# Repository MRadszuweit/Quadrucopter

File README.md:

# Quadrucopter

This repository contains two directories: one with C-code communication of the computer 
with an xbee module via an emulated com port by a FT232 connected to the usb port. 
The other directory contains AVR-C code running on the quadrucopters hardware (ATMEGA64 and ATMEGA8) 
and Eagle files for the electronic layout of different components.

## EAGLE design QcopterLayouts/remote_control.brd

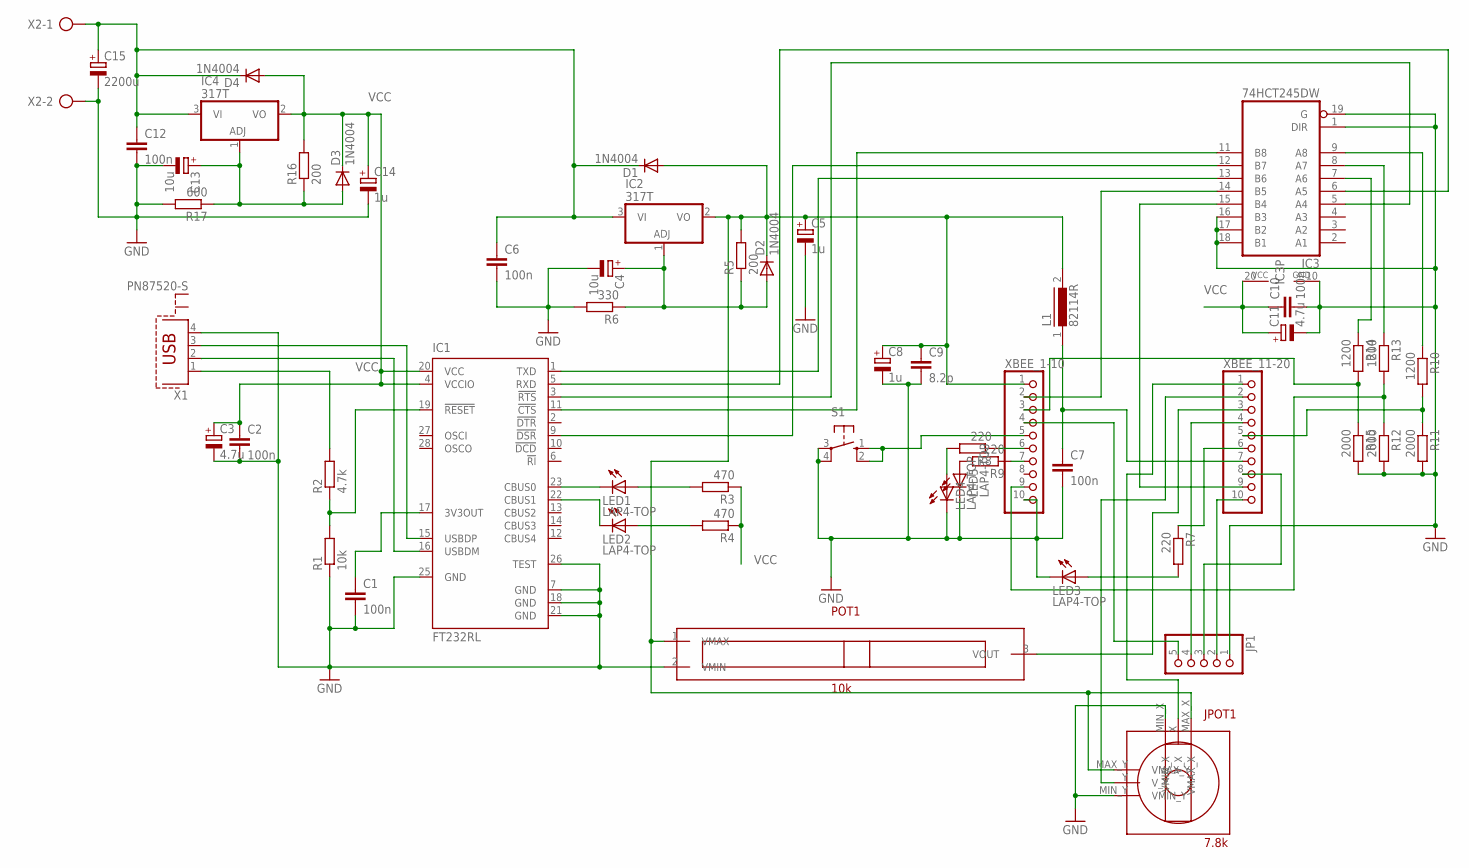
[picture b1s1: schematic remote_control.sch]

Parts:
C1, C6, C7, C12: 100n; C025-030X050
C2, C10: 100n; C0805K
C3, C11: 4.7u; 153CLV-0605
C4, C13: 10u; E5-8,5
C5, C8, C14: 1u; E5-8,5
C9: 8.2p; C025-030X050
C15: 2200u; EB20D
D1, D2, D3, D4: 1N4004; DO41-10
IC1: FT232RL; SSOP28
IC2, IC4: 317T; TO220H
IC3: 74HCT245DW; SO20W
JP1: PINHD-1X5; 1X05
JPOT1: 7.8k; DIL
L1: 82114R
LED1, LED2, LED3, LED4, LED5: LAP4-TOP; P47F-TOP
POT1: 10k; DIL
R1: 10k; 0207/10
R2: 4.7k; 0207/10
R3, R4: 470; 0207/10
R5, R16: 200; 0411/15
R6: 330; 0411/15
R7, R8, R9: 220; 0207/10
R10, R13, R14: 1200; 0207/10
R11, R12, R15: 2000; 0207/10
R17: 600; 0411/15
S1: 40-XX; B3F-40XX
X1: PN87520-S
X2: AK300/2
XBEE_1-10, XBEE_11-20: PINHD-1X10M; 1X10M

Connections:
GND: C1.2, C2.2, C3.-, C4.-, C5.-, C6.2, C7.2, C8.-, C9.2, C10.2, C11.-, C12.2, C13.-, C14.-, C15.-, IC1.7 (GND), IC1.18 (GND), IC1.21 (GND), IC1.25 (GND), IC1.26 (TEST), IC3.1 (DIR), IC3.10 (GND), IC3.16 (B3), IC3.17 (B2), IC3.18 (B1), IC3.19 (G), JP1.1, JPOT1.MIN_X (VMIN_X), JPOT1.MIN_Y (VMIN_Y), LED3.C, LED4.C, LED5.C, POT1.2 (VMIN), R1.1, R6.2, R11.2, R12.2, R15.2, R17.2, S1.3, S1.4 (P1), X1.4, X2.2, XBEE_1-10.10
unnamed: R2.2, X1.1
unnamed: IC1.19 (!RESET), R1.2, R2.1
unnamed: IC1.16 (USBDM), X1.2
unnamed: IC1.15 (USBDP), X1.3
unnamed: C1.1, IC1.17 (3V3OUT)
unnamed: S1.1 (S), S1.2 (S1), XBEE_1-10.5
unnamed: C4.+, D2.A, IC2.1 (ADJ), R5.1, R6.1
unnamed: LED3.A, R7.2
unnamed: IC1.23 (CBUS0), LED1.C
unnamed: IC1.22 (CBUS1), LED2.C
unnamed: LED1.A, R3.2
unnamed: LED2.A, R4.2
unnamed: R7.1, XBEE_11-20.6
unnamed: C7.1, L1.1, XBEE_11-20.7
unnamed: C5.+, C8.+, C9.1, D1.A, D2.C, IC2.2 (VO), JPOT1.MAX_X (VMAX_X), JPOT1.MAX_Y (VMAX_Y), L1.2, POT1.1 (VMAX), R5.2, XBEE_1-10.1
unnamed: R8.1, XBEE_1-10.6
unnamed: LED4.A, R8.2
unnamed: R9.1, XBEE_1-10.7
unnamed: LED5.A, R9.2
unnamed: IC3.9 (A8), R10.1
unnamed: R10.2, R11.1, XBEE_11-20.5
unnamed: R12.1, R13.2, XBEE_1-10.9
unnamed: IC1.11 (!CTS), IC3.11 (B8)
unnamed: IC3.8 (A7), R13.1
unnamed: IC1.9 (!DSR), IC3.12 (B7)
unnamed: R14.2, R15.1, XBEE_1-10.3
unnamed: IC3.7 (A6), R14.1
unnamed: JP1.2, XBEE_11-20.10
unnamed: IC1.1 (TXD), IC3.13 (B6)
unnamed: IC1.5 (RXD), IC3.6 (A5)
unnamed: IC3.14 (B5), XBEE_1-10.2
unnamed: IC1.3 (!RTS), IC3.5 (A4)
unnamed: IC3.15 (B4), XBEE_11-20.9
unnamed: JP1.3, XBEE_11-20.8
unnamed: JP1.4, XBEE_11-20.4
unnamed: JP1.5, XBEE_1-10.4
unnamed: POT1.3 (VOUT), XBEE_11-20.3
unnamed: JPOT1.X (V_X), XBEE_11-20.1
unnamed: JPOT1.Y (V_Y), XBEE_11-20.2
unnamed: C13.+, D3.A, IC4.1 (ADJ), R16.1, R17.1
V: C6.1, C12.1, C15.+, D1.C, D4.C, IC2.3 (VI), IC4.3 (VI), X2.1
VCC: C2.1, C3.+, C10.1, C11.+, C14.+, D3.C, D4.A, IC1.4 (VCCIO), IC1.20 (VCC), IC3.20 (VCC), IC4.2 (VO), R3.1, R4.1, R16.2

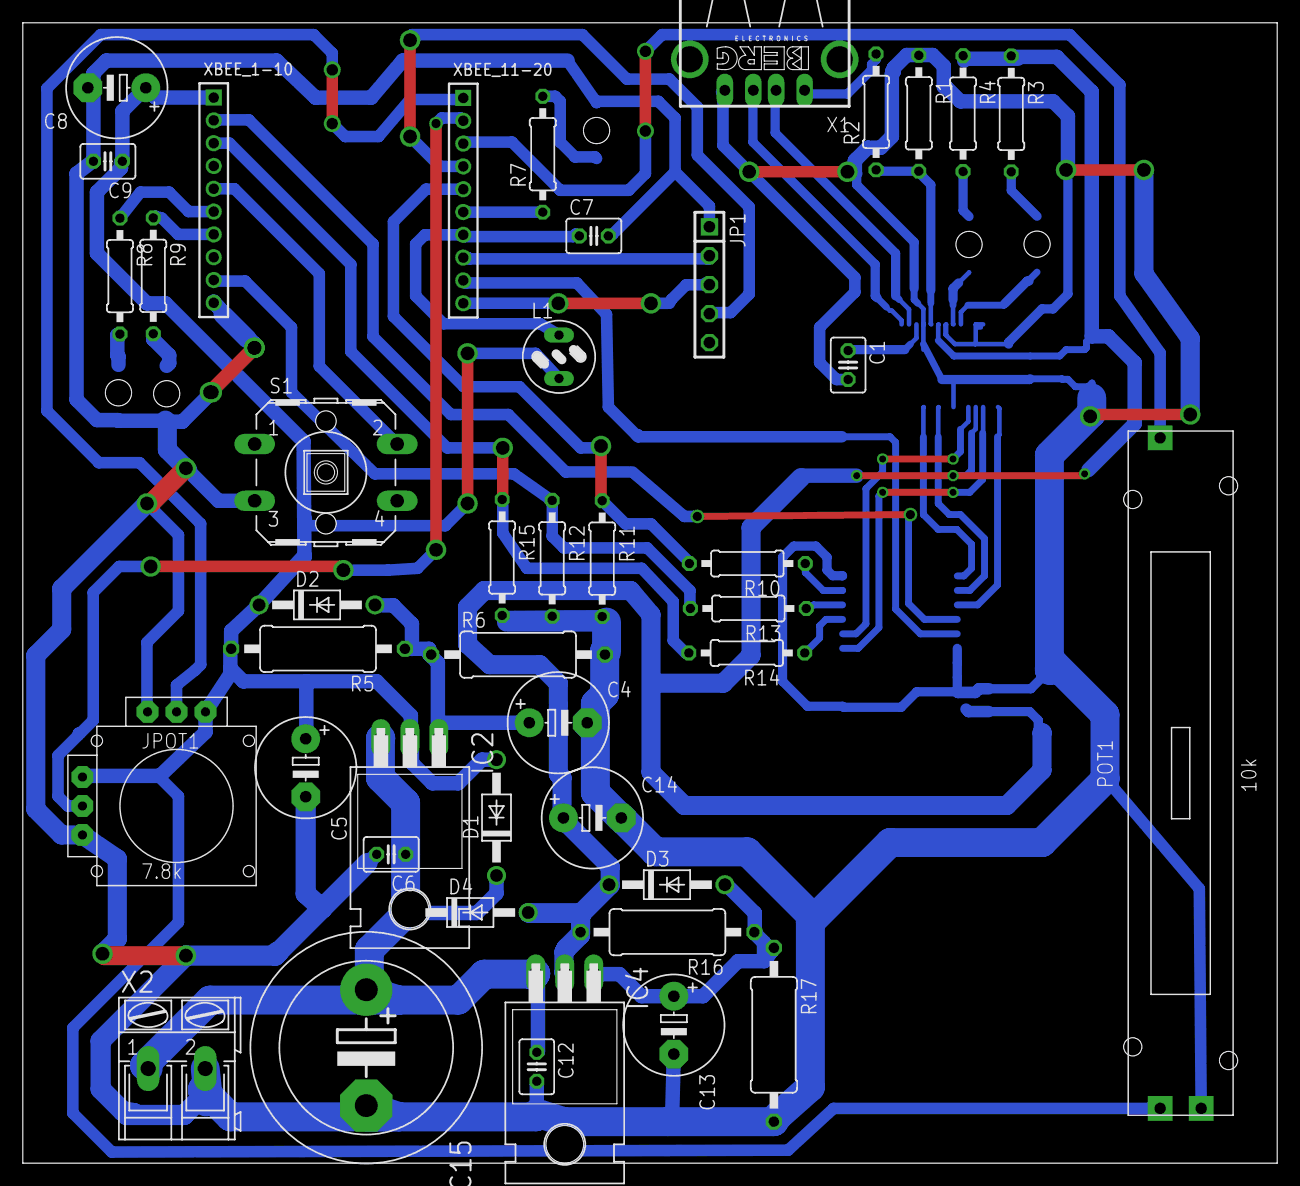
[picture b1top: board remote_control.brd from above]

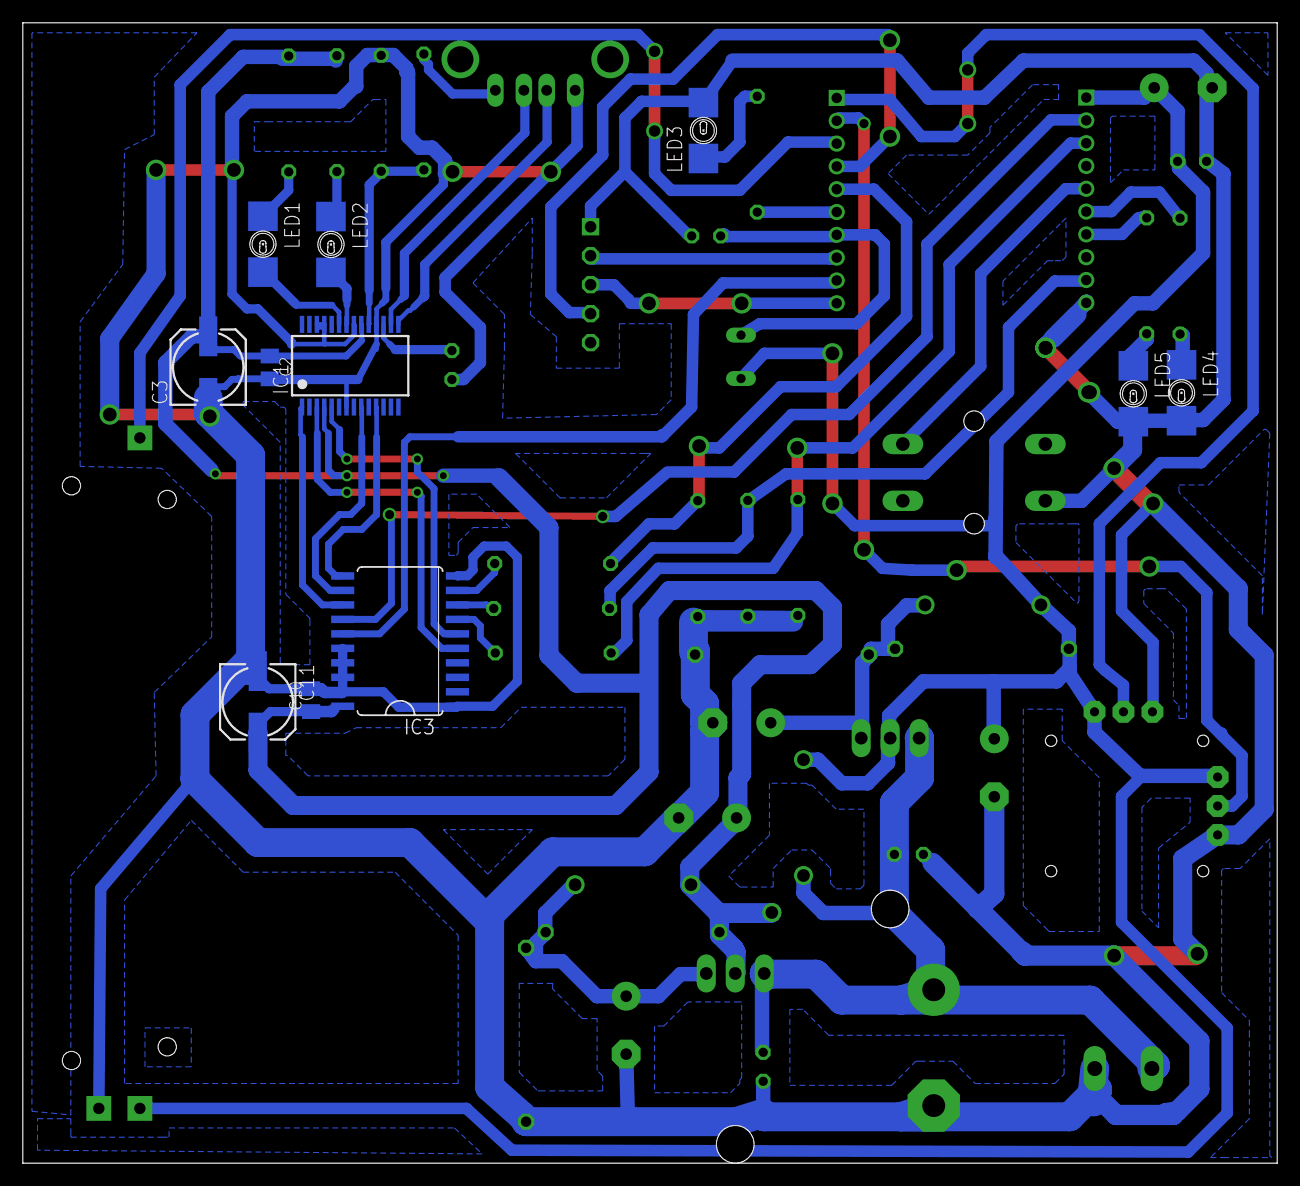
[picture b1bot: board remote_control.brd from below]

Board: 2 copper layers, 110.0 x 100.0 mm, 54 parts (11 on the bottom side), 43 nets.

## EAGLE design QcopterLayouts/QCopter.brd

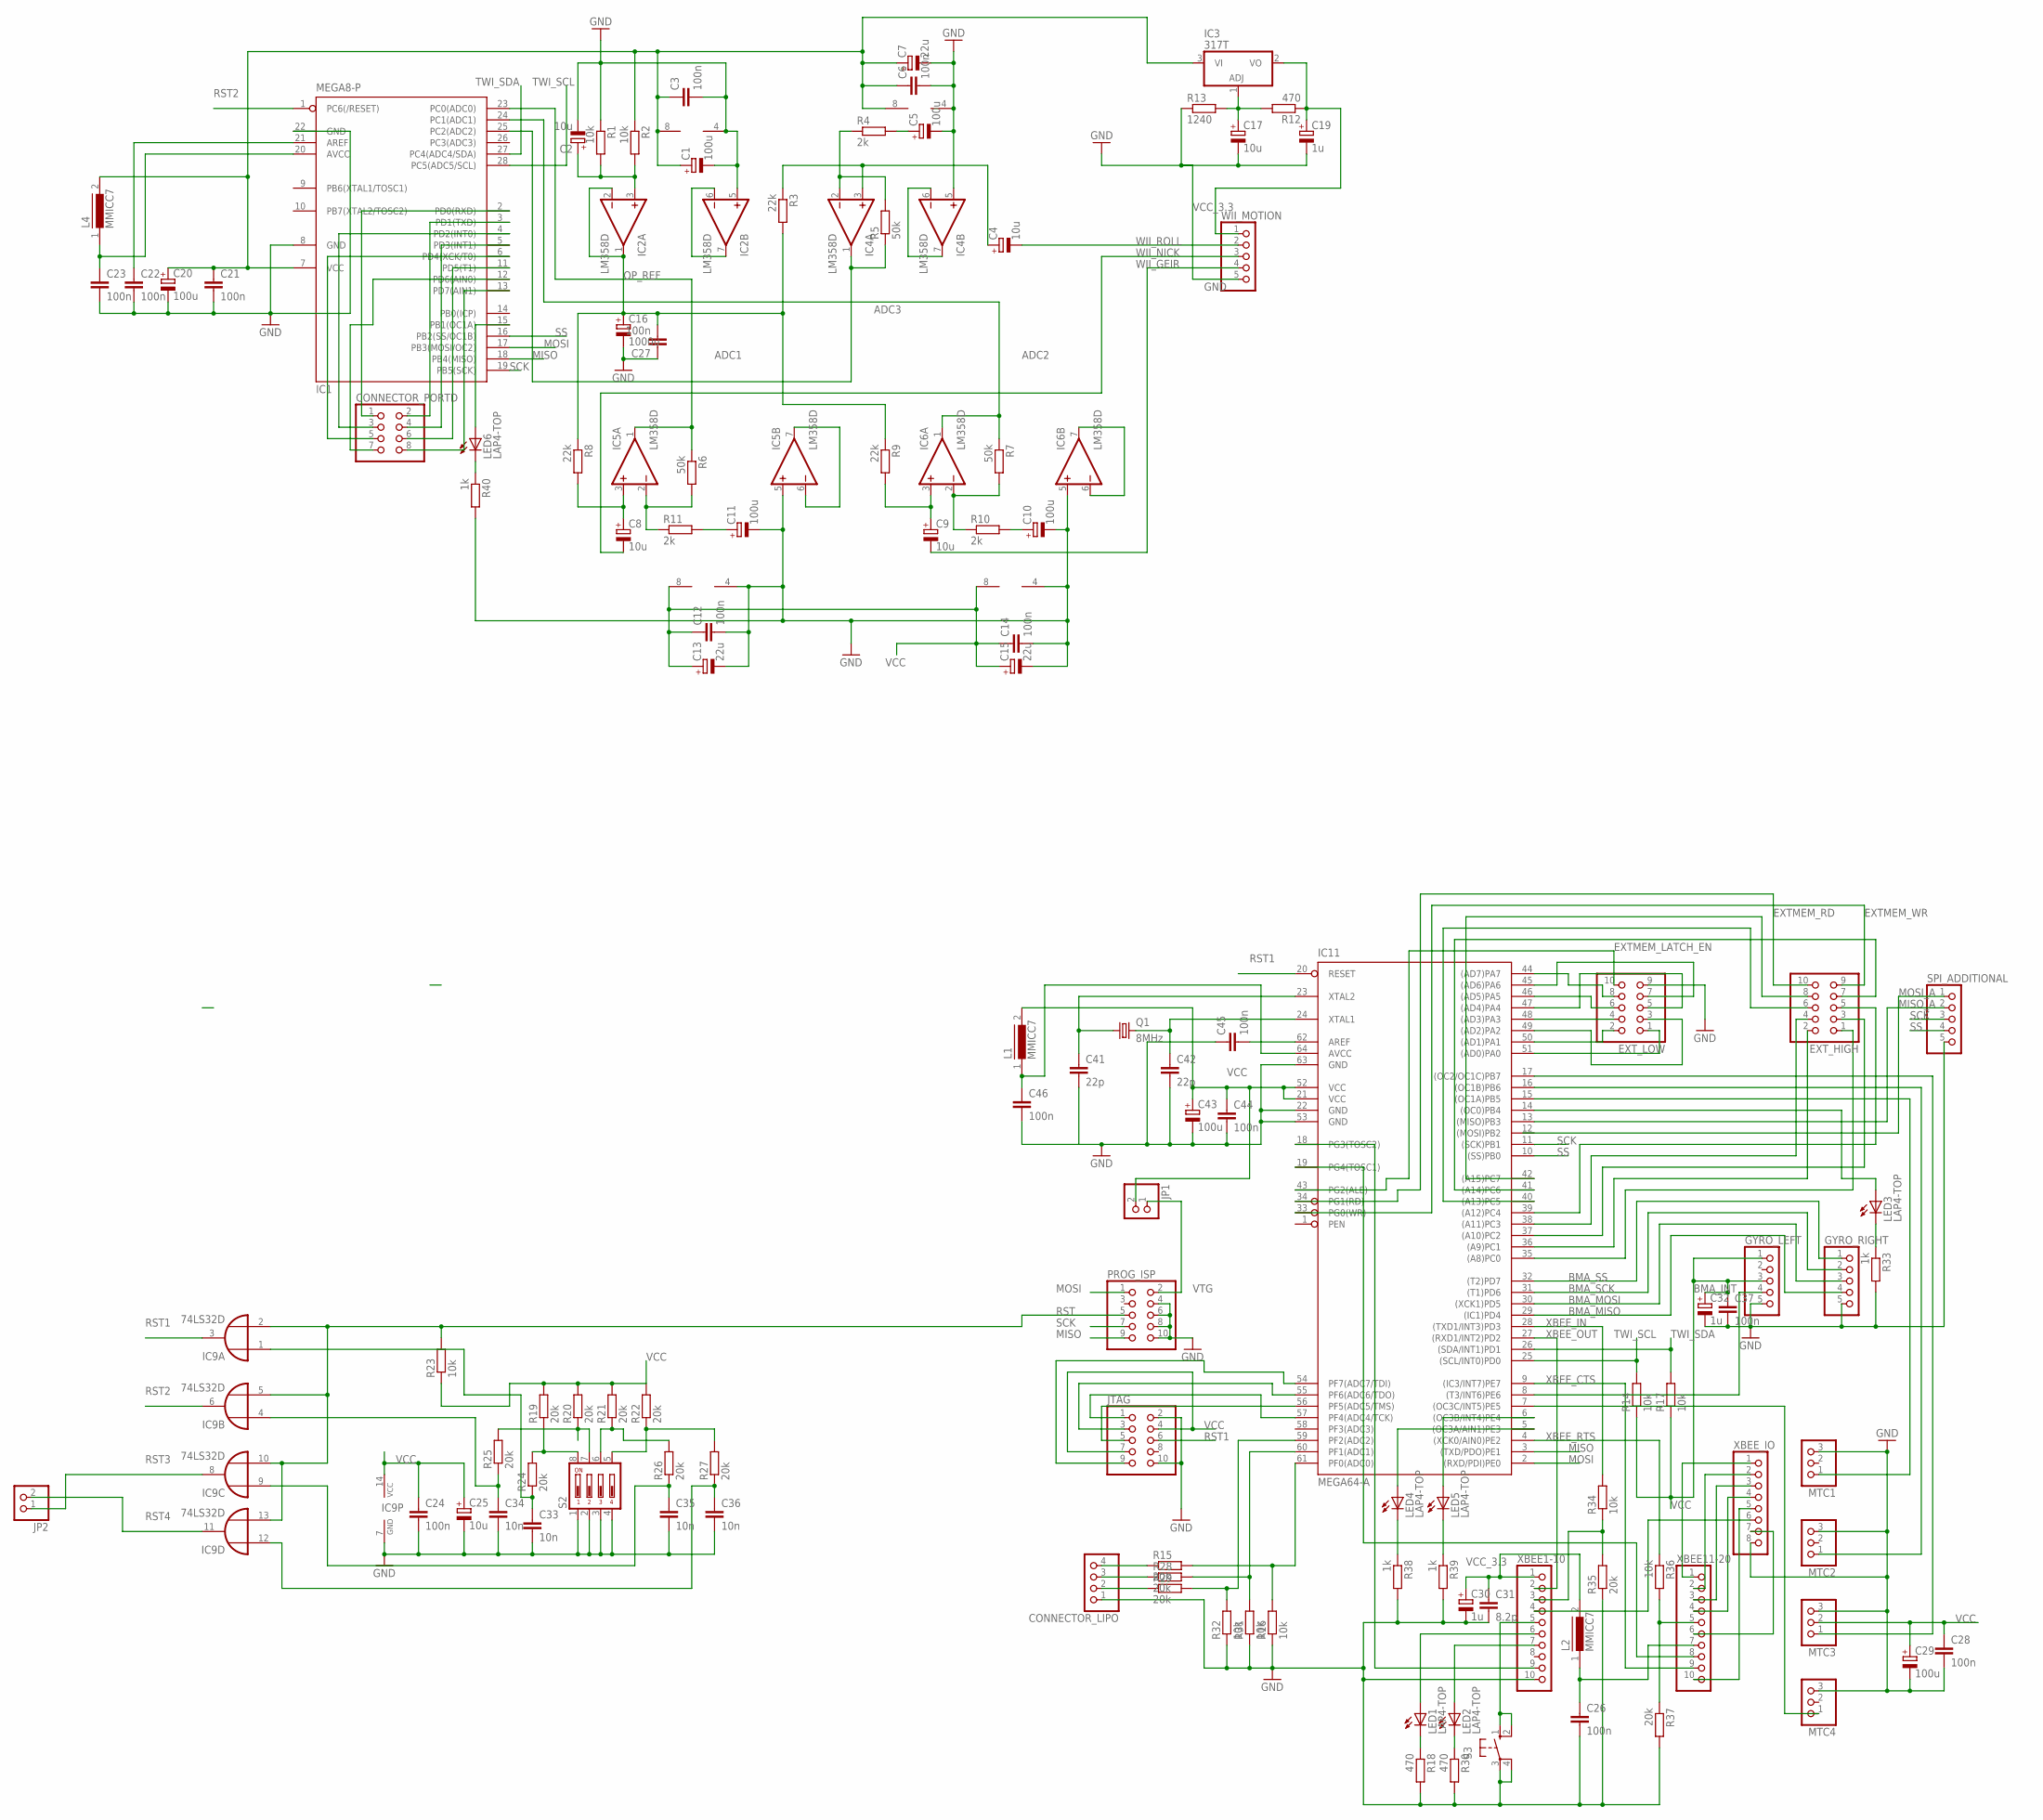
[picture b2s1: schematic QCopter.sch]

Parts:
C1, C5, C10, C11: 100u; 153CLV-0505
C2, C4, C8, C9, C25: 10u; 153CLV-0505
C3, C6, C12, C14, C24, C26, C27, C28, C37, C44, C45, C46: 100n; C0805K
C7, C13, C15: 22u; 153CLV-0505
C16: 1000u; E3,5-10
C17: 10u; E5-6
C19: 1u; E5-6
C20: 100u; E5-6
C21, C22, C23: 100n; C025-025X050
C29, C43: 100u; 153CLV-0605
C30, C32: 1u; 153CLV-0605
C31: 8.2p; C025-024X044
C33, C34, C35, C36: 10n; C0805K
C41, C42: 22p; C025-025X050
CONNECTOR_LIPO: PINHD-1X4; 1X04
CONNECTOR_PORTD: PINHD-2X4; 2X04
EXT_HIGH: PINHD-2X5; 2X05
EXT_LOW: PINHD-2X5; 2X05
GYRO_LEFT: PINHD-1X5; 1X05
GYRO_RIGHT: PINHD-1X5; 1X05
IC1: MEGA8-P; DIL28-3
IC2, IC4, IC5, IC6: LM358D; SO08
IC3: 317T; TO220H
IC9: 74LS32D; SO14
IC11: MEGA64-A; TQFP64
JP1, JP2: PINHD-1X2; 1X02
JTAG: PINHD-2X5; 2X05
L1, L2, L4: MMICC7
LED1, LED2, LED3, LED4, LED5, LED6: LAP4-TOP; P47F-TOP
MTC1, MTC2, MTC3, MTC4: PINHD-1X3; 1X03
PROG_ISP: PINHD-2X5; 2X05
Q1: 8MHz; HC49/S
R1, R2, R14, R16, R17, R23, R31, R32, R34, R36: 10k; R1206
R3, R8, R9: 22k; R1206
R4, R10, R11: 2k; R1206
R5, R6, R7: 50k; R1206
R12: 470; 0414/15
R13: 1240; 0414/15
R15, R19, R20, R21, R22, R24, R25, R26, R28, R29, R35, R37: 20k; R1206
R18, R30: 470; R1206
R27: 20k; R1206W
R33, R38, R39, R40: 1k; R1206
S2: DS04; DS-04
S3: 10-XX; B3F-10XX
SPI_ADDITIONAL: PINHD-1X5; 1X05
WII_MOTION: PINHD-1X5; 1X05
XBEE1-10, XBEE11-20: PINHD-1X10M; 1X10M
XBEE_IO: PINHD-1X8; 1X08

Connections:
ADC1: IC1.23 (PC0(ADC0)), IC5.1 (OUT), R6.1
ADC2: IC1.24 (PC1(ADC1)), IC6.1 (OUT), R7.1
ADC3: IC1.25 (PC2(ADC2)), IC4.1 (OUT), R5.1
BMA_INT: GYRO_LEFT.4, IC11.8 ((T3/INT6)PE6)
BMA_MISO: GYRO_RIGHT.4, IC11.29 ((IC1)PD4)
BMA_MOSI: GYRO_RIGHT.3, IC11.30 ((XCK1)PD5)
BMA_SCK: GYRO_RIGHT.2, IC11.31 ((T1)PD6)
BMA_SS: GYRO_RIGHT.1, IC11.32 ((T2)PD7)
EXTMEM_LATCH_EN: EXT_LOW.10, IC11.43 (PG2(ALE))
EXTMEM_RD: EXT_HIGH.10, IC11.34 (PG1(RD))
EXTMEM_WR: EXT_HIGH.9, IC11.33 (PG0(WR))
EXT_LOW: EXT_LOW.1, IC11.51 ((AD0)PA0)
GND: C1.-, C2.-, C3.2, C5.-, C6.2, C7.-, C10.-, C11.-, C12.2, C13.-, C14.2, C15.-, C16.-, C17.-, C19.-, C20.-, C21.2, C22.2, C23.2, C24.2, C25.-, C26.2, C27.1, C28.2, C29.-, C30.-, C31.2, C32.-, C33.2, C34.2, C35.2, C36.2, C37.2, C41.2, C42.2, C43.-, C44.2, C45.1, C46.2, CONNECTOR_LIPO.1, EXT_LOW.9, GYRO_LEFT.5, GYRO_RIGHT.5, IC1.8 (GND), IC1.22 (GND), IC2.4 (V-), IC2.5 (+IN), IC4.4 (V-), IC4.5 (+IN), IC5.4 (V-), IC5.5 (+IN), IC6.4 (V-), IC6.5 (+IN), IC9.7 (GND), IC11.22 (GND), IC11.53 (GND), IC11.63 (GND), JTAG.2, JTAG.10, MTC1.3, MTC2.3, MTC3.3, MTC4.3, PROG_ISP.4, PROG_ISP.6, PROG_ISP.8, PROG_ISP.10, R1.1, R13.1, R16.1, R18.2, R30.2, R31.1, R32.1, R33.2, R35.1, R37.2, R38.2, R39.2, R40.2, S2.1, S2.2, S2.3, S2.4, S3.3, S3.4 (P1), SPI_ADDITIONAL.5, WII_MOTION.5, XBEE1-10.10, XBEE_IO.8
MISO: IC1.18 (PB4(MISO)), IC11.3 ((TXD/PDO)PE1), PROG_ISP.9
MISO_A: IC11.13 ((MISO)PB3), SPI_ADDITIONAL.2
MOSI: IC1.17 (PB3(MOSI/OC2)), IC11.2 ((RXD/PDI)PE0), PROG_ISP.1
MOSI_A: SPI_ADDITIONAL.1
unnamed: C2.+, IC2.3 (+IN), R1.2, R2.2
unnamed: IC2.6 (-IN), IC2.7 (OUT)
unnamed: IC4.6 (-IN), IC4.7 (OUT)
unnamed: C4.+, IC4.3 (+IN), R3.1
unnamed: IC11.15 ((OC1A)PB5), MTC1.1
unnamed: IC11.16 ((OC1B)PB6), MTC2.1
unnamed: C5.+, R4.2
unnamed: IC4.2 (-IN), R4.1, R5.2
unnamed: IC5.2 (-IN), R6.2, R11.1
unnamed: CONNECTOR_PORTD.1, IC1.2 (PD0(RXD))
unnamed: IC6.2 (-IN), R7.2, R10.1
unnamed: C17.+, IC3.1 (ADJ), R12.2, R13.2
unnamed: IC5.6 (-IN), IC5.7 (OUT)
unnamed: IC6.6 (-IN), IC6.7 (OUT)
unnamed: C11.+, R11.2
unnamed: C22.1, IC1.21 (AREF)
unnamed: C8.+, IC5.3 (+IN), R8.2
unnamed: C9.+, IC6.3 (+IN), R9.2
unnamed: C41.1, IC11.23 (XTAL2), Q1.1
unnamed: C42.1, IC11.24 (XTAL1), Q1.2
unnamed: C10.+, R10.2
unnamed: C23.1, IC1.20 (AVCC), L4.1
unnamed: CONNECTOR_PORTD.2, IC1.3 (PD1(TXD))
unnamed: IC11.17 ((OC2/OC1C)PB7), MTC3.1
unnamed: IC11.7 ((OC3C/INT5)PE5), MTC4.1
unnamed: CONNECTOR_PORTD.3, IC1.4 (PD2(INT0))
unnamed: CONNECTOR_PORTD.4, IC1.5 (PD3(INT1))
unnamed: CONNECTOR_PORTD.5, IC1.6 (PD4(XCK/T0))
unnamed: CONNECTOR_PORTD.6, IC1.11 (PD5(T1))
unnamed: CONNECTOR_PORTD.7, IC1.12 (PD6(AIN0))
unnamed: CONNECTOR_PORTD.8, IC1.13 (PD7(AIN1))
unnamed: CONNECTOR_LIPO.4, R15.1
unnamed: LED1.C, R18.1
unnamed: LED2.C, R30.1
unnamed: C26.1, L2.1, XBEE11-20.7
unnamed: C45.2, IC11.62 (AREF)
unnamed: LED1.A, XBEE1-10.6
unnamed: IC11.61 (PF0(ADC0)), R15.2, R16.2
unnamed: LED2.A, XBEE1-10.7
unnamed: C46.1, IC11.64 (AVCC), L1.1
unnamed: XBEE11-20.1, XBEE_IO.1
unnamed: S3.1 (S), S3.2 (S1), XBEE1-10.5
unnamed: XBEE11-20.2, XBEE_IO.2
unnamed: CONNECTOR_LIPO.3, R28.1
unnamed: XBEE11-20.3, XBEE_IO.3
unnamed: XBEE11-20.4, XBEE_IO.4
unnamed: IC11.14 ((OC0)PB4), LED3.A
unnamed: LED3.C, R33.1
unnamed: EXT_HIGH.1, IC11.35 ((A8)PC0)
unnamed: CONNECTOR_LIPO.2, R29.1
unnamed: R19.1, R24.2, S2.8
unnamed: R21.1, R26.2, S2.6
unnamed: C35.1, IC9.9 (I0), R26.1
unnamed: C36.1, IC9.12 (I0), R27.1
unnamed: R20.1, R25.2, S2.7
unnamed: C33.1, IC9.1 (I0), R24.1
unnamed: C34.1, IC9.4 (I0), R25.1
unnamed: R22.1, R27.2, S2.5
unnamed: XBEE11-20.10, XBEE_IO.5
unnamed: IC11.60 (PF1(ADC1)), R28.2, R31.2
unnamed: IC11.59 (PF2(ADC2)), R29.2, R32.2
unnamed: EXT_LOW.2, IC11.50 ((AD1)PA1)
unnamed: EXT_LOW.3, IC11.49 ((AD2)PA2)
unnamed: EXT_LOW.4, IC11.48 ((AD3)PA3)
unnamed: EXT_LOW.5, IC11.47 ((AD4)PA4)
unnamed: EXT_LOW.6, IC11.46 ((AD5)PA5)
unnamed: EXT_LOW.7, IC11.45 ((AD6)PA6)
unnamed: EXT_LOW.8, IC11.44 ((AD7)PA7)
unnamed: EXT_HIGH.2, IC11.36 ((A9)PC1)
unnamed: EXT_HIGH.3, IC11.37 ((A10)PC2)
unnamed: EXT_HIGH.4, IC11.38 ((A11)PC3)
unnamed: EXT_HIGH.5, IC11.39 ((A12)PC4)
unnamed: EXT_HIGH.6, IC11.40 ((A13)PC5)
unnamed: EXT_HIGH.7, IC11.41 ((A14)PC6)
unnamed: EXT_HIGH.8, IC11.42 ((A15)PC7)
unnamed: IC11.18 (PG3(TOSC2)), XBEE1-10.9
unnamed: IC11.19 (PG4(TOSC1)), XBEE11-20.8
unnamed: XBEE1-10.4, XBEE_IO.6
unnamed: XBEE11-20.6, XBEE_IO.7
unnamed: R34.1, R35.2, XBEE1-10.3
unnamed: IC11.57 (PF4(ADC4/TCK)), JTAG.1
unnamed: R36.2, R37.1, XBEE11-20.5
unnamed: IC11.55 (PF6(ADC6/TDO)), JTAG.3
unnamed: IC11.56 (PF5(ADC5/TMS)), JTAG.5
unnamed: LED6.C, R40.1
unnamed: IC11.54 (PF7(ADC7/TDI)), JTAG.9
unnamed: LED4.C, R38.1
unnamed: LED5.C, R39.1
unnamed: IC11.5 ((OC3A/AIN1)PE3), LED4.A
unnamed: IC11.6 ((OC3B/INT4)PE4), LED5.A
unnamed: IC1.15 (PB1(OC1A)), LED6.A
OP_REF: C16.+, C27.2, IC2.1 (OUT), IC2.2 (-IN), R3.2, R8.1, R9.1
RST: IC9.2 (I1), IC9.5 (I1), IC9.10 (I1), IC9.13 (I1), PROG_ISP.5, R23.2
RST1: IC9.3 (O), IC11.20 (RESET), JTAG.6
RST2: IC1.1 (PC6(/RESET)), IC9.6 (O)
RST3: IC9.8 (O), JP2.1
RST4: IC9.11 (O), JP2.2
SCK: IC1.19 (PB5(SCK)), IC11.11 ((SCK)PB1), PROG_ISP.7, SPI_ADDITIONAL.3
SS: IC1.16 (PB2(SS/OC1B)), IC11.10 ((SS)PB0), SPI_ADDITIONAL.4
TWI_SCL: IC1.28 (PC5(ADC5/SCL)), IC11.25 ((SCL/INT0)PD0), R14.2
TWI_SDA: IC1.27 (PC4(ADC4/SDA)), IC11.26 ((SDA/INT1)PD1), R17.2
VCC: C1.+, C3.1, C6.1, C7.+, C12.1, C13.+, C14.1, C15.+, C20.+, C21.1, C24.1, C25.+, C28.1, C29.+, C32.+, C37.1, C43.+, C44.1, GYRO_LEFT.1, GYRO_LEFT.3, IC1.7 (VCC), IC2.8 (V+), IC3.3 (VI), IC4.8 (V+), IC5.8 (V+), IC6.8 (V+), IC9.14 (VCC), IC11.21 (VCC), IC11.52 (VCC), JP1.2, JTAG.4, JTAG.7, L1.2, L4.2, MTC3.2, R2.1, R14.1, R17.1, R19.2, R20.2, R21.2, R22.2, R23.1
VCC_3.3: C19.+, C30.+, C31.1, IC3.2 (VO), L2.2, R12.1, WII_MOTION.1, XBEE1-10.1
VTG: JP1.1, PROG_ISP.2
WII_GEIR: C9.-, WII_MOTION.4
WII_NICK: C8.-, WII_MOTION.3
WII_ROLL: C4.-, WII_MOTION.2
XBEE_CTS: IC11.9 ((IC3/INT7)PE7), XBEE11-20.9
XBEE_IN: IC11.28 ((TXD1/INT3)PD3), R34.2
XBEE_OUT: IC11.27 ((RXD1/INT2)PD2), XBEE1-10.2
XBEE_RTS: IC11.4 ((XCK0/AIN0)PE2), R36.1

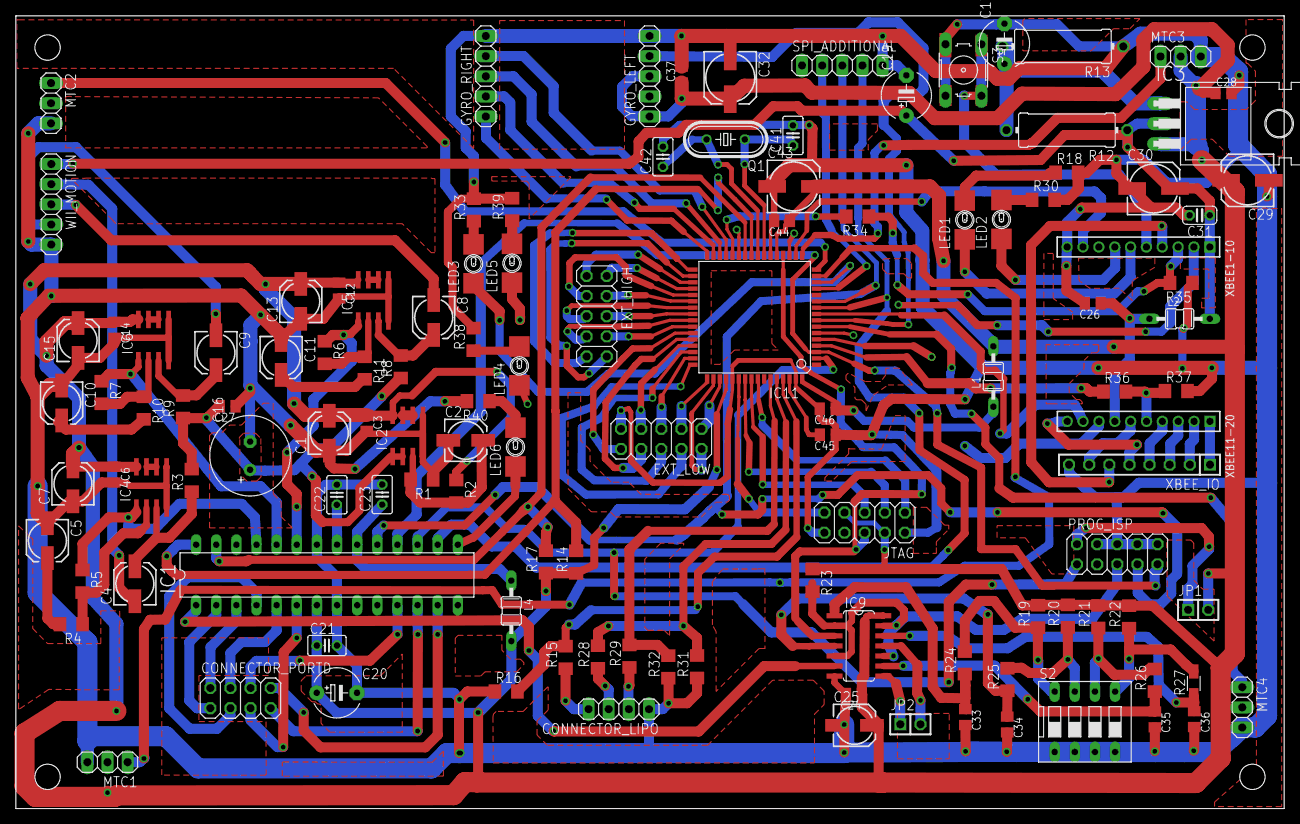
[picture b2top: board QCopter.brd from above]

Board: 2 copper layers, 160.0 x 100.0 mm, 121 parts (0 on the bottom side), 127 nets.

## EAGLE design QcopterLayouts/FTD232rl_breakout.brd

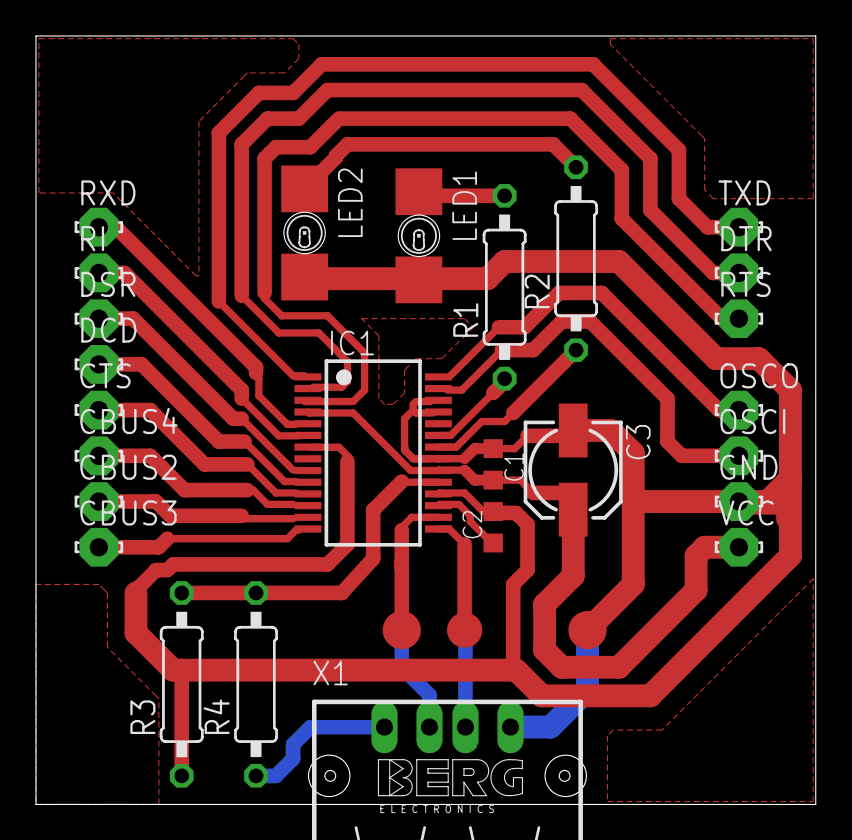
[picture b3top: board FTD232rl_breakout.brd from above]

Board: 2 copper layers, 43.3 x 42.7 mm, 26 parts (0 on the bottom side), 10 nets.

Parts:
C1, C2: 100n; C0603K
C3: 153CLV-0505
CBUS2, CBUS3, CBUS4: LSP10
CTS: LSP10
DCD: LSP10
DSR: LSP10
DTR: LSP10
GND: LSP10
IC1: FT232RL; SSOP28
LED1, LED2: LRP4-TOP; P47F-TOP
OSCI: LSP10
OSCO: LSP10
R1, R2: 270; 0207/10
R3: 10k; 0207/10
R4: 4k7; 0207/10
RI: LSP10
RTS: LSP10
RXD: LSP10
TXD: LSP10
VCC: LSP10
X1: PN87520

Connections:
GND: C1.1, C2.2, C3.-, GND.MP, IC1.7, IC1.18, IC1.21, IC1.25, IC1.26, LED1.C, LED2.C, X1.4
unnamed: IC1.23, R1.1
unnamed: IC1.22, R2.1
unnamed: LED2.A, R2.2
unnamed: LED1.A, R1.2
unnamed: IC1.15, X1.3
unnamed: IC1.16, X1.2
unnamed: IC1.19, R3.2, R4.2
unnamed: C1.2, C3.+, IC1.4, IC1.20, VCC.MP
unnamed: C2.1, IC1.17

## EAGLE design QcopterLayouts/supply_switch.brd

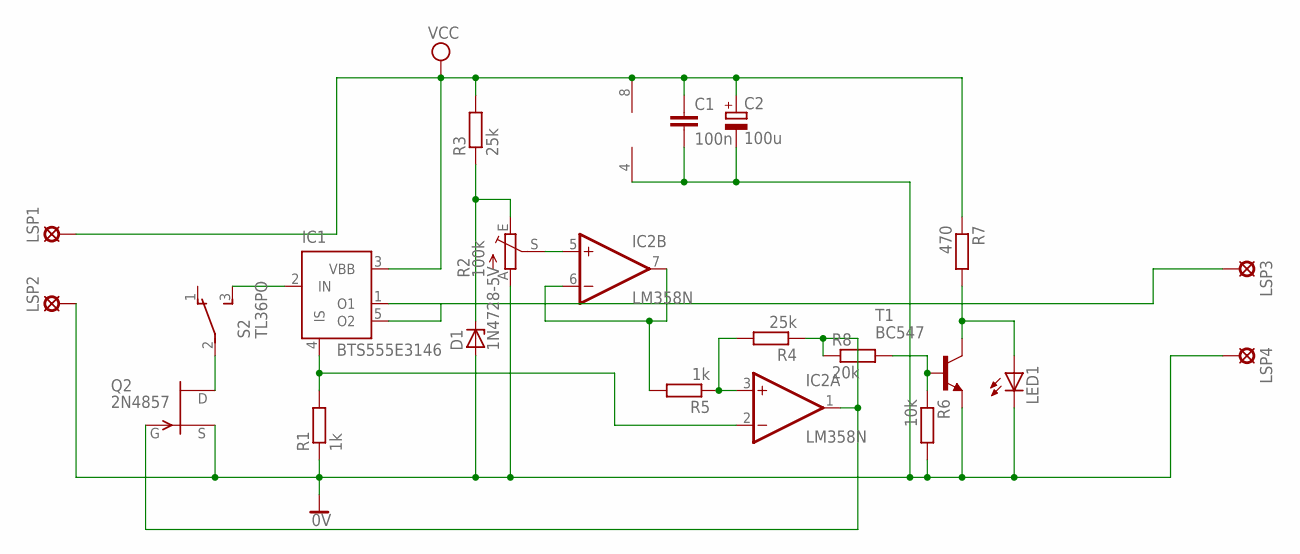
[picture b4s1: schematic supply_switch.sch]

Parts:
C1: 100n; C025-030X050
C2: 100u; E3,5-10
D1: 1N4728-5V; DO41Z10
IC1: BTS555E3146; TO220-52
IC2: LM358N; DIL08
LED1: LED5MM
LSP1, LSP2, LSP3, LSP4: SE14
Q2: 2N4857; TO18
R1, R5: 1k; 0207/15
R2: 100k; CA6H
R3, R4: 25k; 0207/15
R6: 10k; 0207/15
R7: 470; 0207/15
R8: 20k; 0207/15
S2: TL36PO; TL3XPO
T1: BC547; TO92

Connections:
0V: C1.2, C2.-, D1.A, IC2.4 (V-), LED1.K (C), LSP2.MP, LSP4.MP, Q2.1 (S), R1.1, R2.A, R6.2, T1.1 (E)
unnamed: IC1.1 (O1), IC1.5 (O2), LSP3.MP
unnamed: Q2.2 (D), S2.2
unnamed: IC1.2 (IN), S2.3 (S)
unnamed: IC2.6 (-IN), IC2.7 (OUT), R5.2
unnamed: IC2.5 (+IN), R2.S
unnamed: D1.C, R2.E, R3.1
unnamed: R6.1, R8.2, T1.2 (B)
unnamed: IC2.3 (+IN), R4.2, R5.1
unnamed: IC2.1 (OUT), Q2.3 (G), R4.1, R8.1
unnamed: IC1.4 (IS), IC2.2 (-IN), R1.2
unnamed: LED1.A, R7.2, T1.3 (C)
VCC: C1.1, C2.+, IC1.3 (VBB), IC2.8 (V+), LSP1.MP, R3.2, R7.1

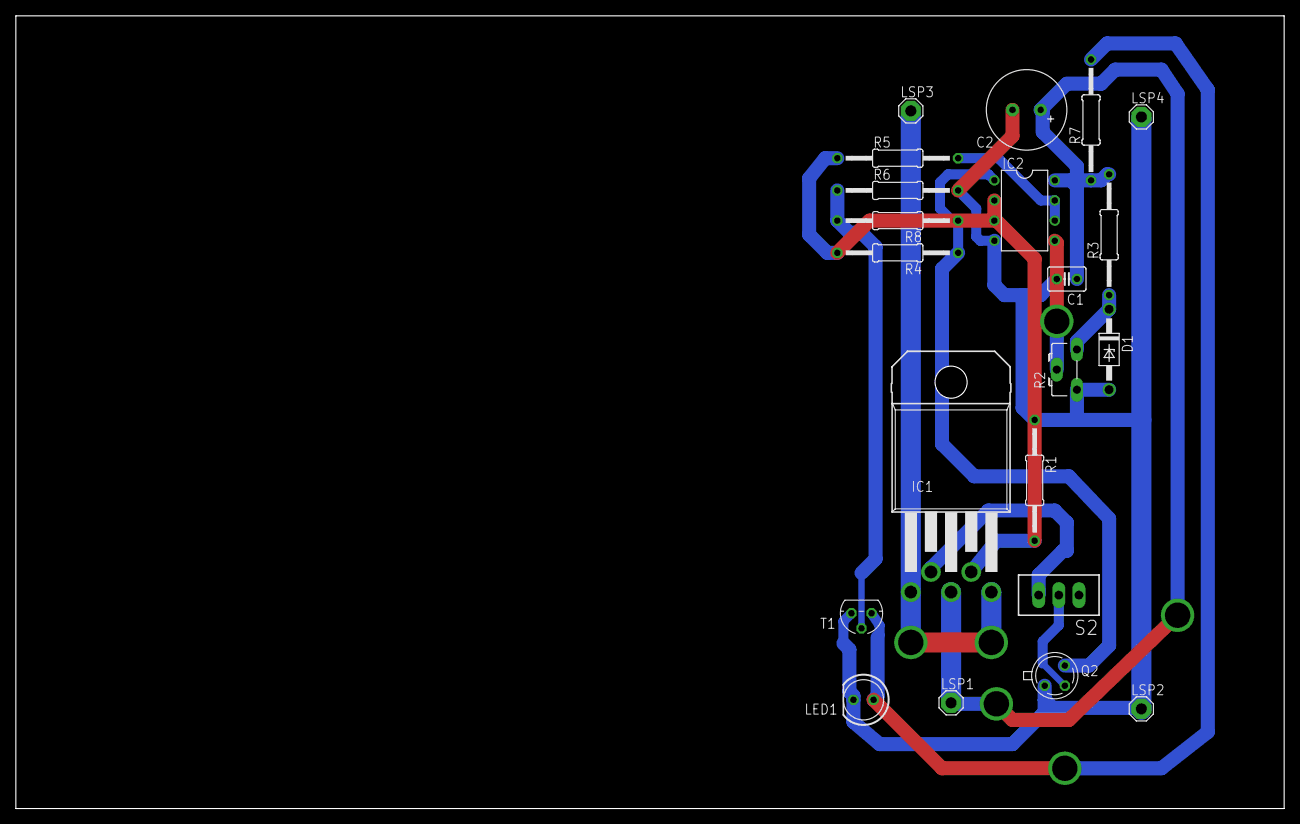
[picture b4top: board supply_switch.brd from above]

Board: 2 copper layers, 160.0 x 100.0 mm, 21 parts (0 on the bottom side), 13 nets.

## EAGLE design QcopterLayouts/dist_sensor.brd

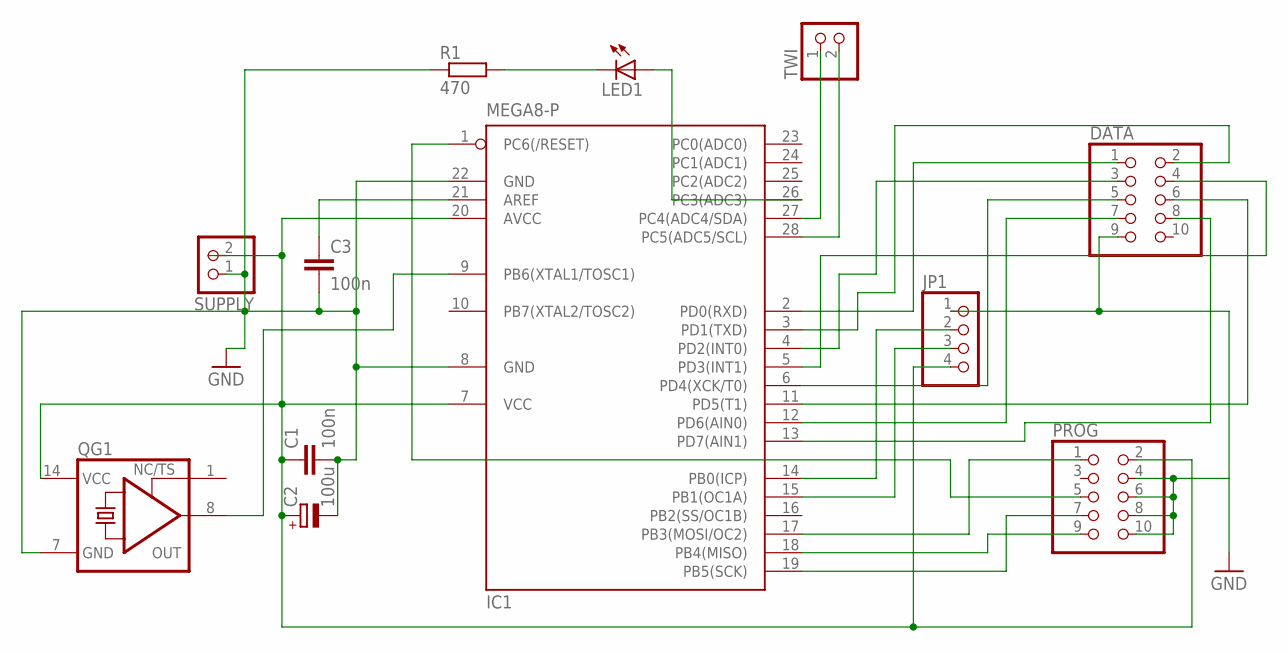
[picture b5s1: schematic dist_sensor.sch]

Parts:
C1, C3: 100n; C025-025X050
C2: 100u; E5-8,5
DATA: PINHD-2X5; 2X05
IC1: MEGA8-P; DIL28-3
JP1: PINHD-1X4; 1X04
LED1: LED5MM
PROG: PINHD-2X5; 2X05
QG1: XO-14; DIL14S
R1: 470; 0207/10
SUPPLY: PINHD-1X2; 1X02
TWI: PINHD-1X2; 1X02

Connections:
GND: C1.2, C2.-, C3.2, DATA.9, IC1.8 (GND), IC1.22 (GND), JP1.1, PROG.4, PROG.6, PROG.8, PROG.10, QG1.7 (GND), R1.1, SUPPLY.1
unnamed: IC1.17 (PB3(MOSI/OC2)), PROG.1
unnamed: IC1.18 (PB4(MISO)), PROG.9
unnamed: IC1.19 (PB5(SCK)), PROG.7
unnamed: C1.1, C2.+, IC1.7 (VCC), IC1.20 (AVCC), JP1.4, PROG.2, QG1.14 (VCC), SUPPLY.2
unnamed: IC1.1 (PC6(/RESET)), PROG.5
unnamed: DATA.1, IC1.2 (PD0(RXD))
unnamed: DATA.2, IC1.3 (PD1(TXD))
unnamed: IC1.27 (PC4(ADC4/SDA)), TWI.1
unnamed: DATA.4, IC1.5 (PD3(INT1))
unnamed: DATA.3, IC1.4 (PD2(INT0))
unnamed: DATA.5, IC1.6 (PD4(XCK/T0))
unnamed: DATA.6, IC1.11 (PD5(T1))
unnamed: DATA.8, IC1.13 (PD7(AIN1))
unnamed: IC1.14 (PB0(ICP)), JP1.2
unnamed: DATA.7, IC1.12 (PD6(AIN0))
unnamed: IC1.15 (PB1(OC1A)), JP1.3
unnamed: C3.1, IC1.21 (AREF)
unnamed: IC1.9 (PB6(XTAL1/TOSC1)), QG1.8 (OUT)
unnamed: IC1.28 (PC5(ADC5/SCL)), TWI.2
unnamed: IC1.26 (PC3(ADC3)), LED1.A
unnamed: LED1.K (C), R1.2

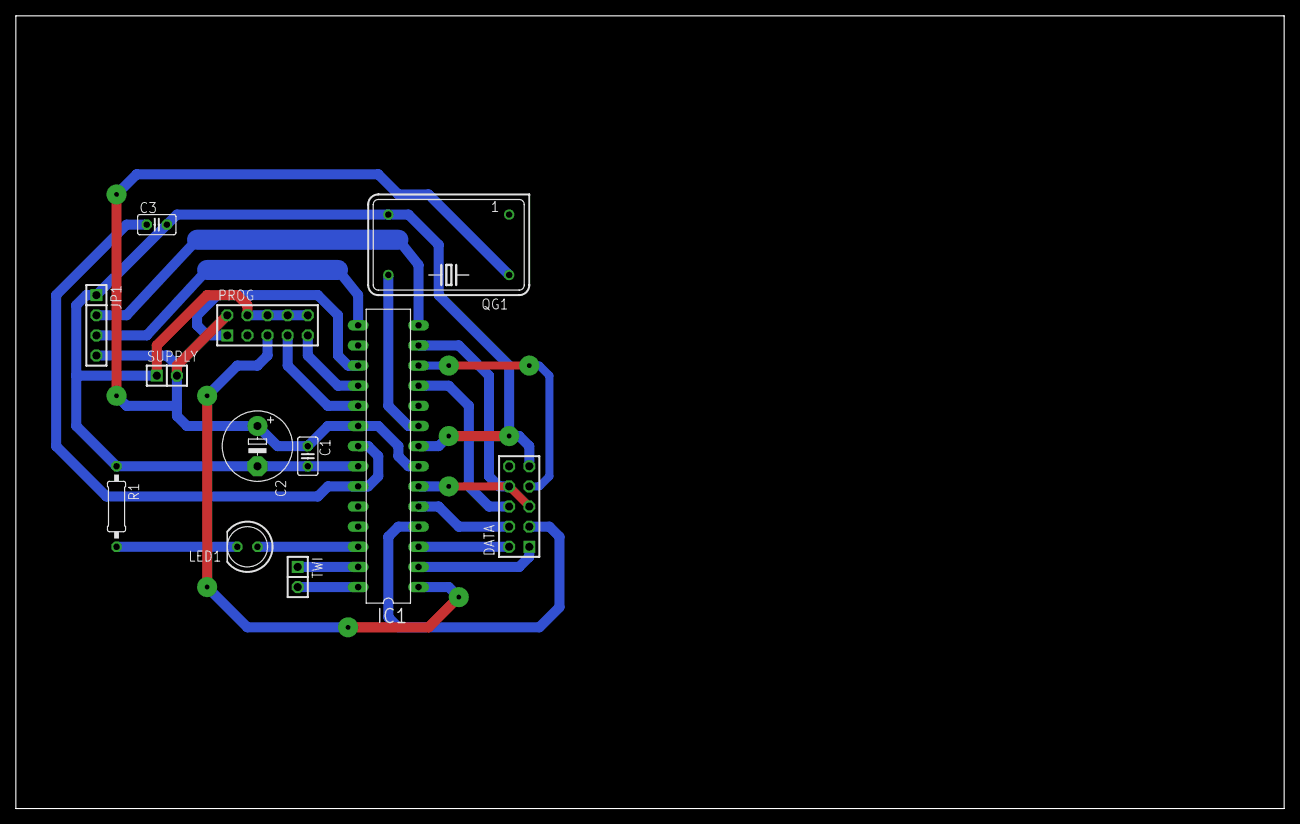
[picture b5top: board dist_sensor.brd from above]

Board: 2 copper layers, 160.0 x 100.0 mm, 12 parts (0 on the bottom side), 22 nets.

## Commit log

2018-01-23 Update README.md
    Initial commit
2018-01-23 Add files via upload
    Initial commit of the code for serial communication of the computer with the xbee module.
2018-01-23 Add files via upload
    Programs running on the main CPU of the quadrucopter (qcopter) and a secon external ADC (qcopterAD) and some libs in AVR-C
2018-01-23 Add files via upload
    Eagle files for electronic layouts
